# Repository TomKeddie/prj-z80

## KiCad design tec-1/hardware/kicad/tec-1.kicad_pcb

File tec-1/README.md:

# Ideas

## Notes
- Need xtal for clock (issue 14) 8MHZ for Z80A
- display and tape (issue 15 page 47)
- single stepper (issue 15 page 51)
- Z80B can do 6MHz
- Add clock generation to cpld (2/4/6MHz)
- Mux keyboard and ft2232 through cpld for keyboard emulation
- flash A18 is wired to z80 A12 to split the chip in two
- shift button (issue 13 page 10)
- 8x8 display (issue 11 pag 22)
- lcd interface (issue 15 page 49)
- use 74ABT574 for octal latch

## CPLDs
### Address (100%)
- memory address decode and bank select flash
- memory address decode sram x 2
- cpu clock divide
- io address decode for keyboard, led display
- single step

### Data (100%)
- keyboard mux
- led display column store
- speaker

### Peripheral (100%)
- Data bus {8 pins}
- Address bus {3 pins}
- Control bus {2 pins}
- 8x8 led store (x and y) {16 pins}
- io address decode for 8x8 led {no pins}
- io address decode for lcd display {1 pin}
- jmon keyboard {1 pin}

## Memory Map
| Address Range | Purpose | Notes | 
|:-------------:|:-------------:|:-------------|
| 0000-07FF     | 2k ROM | Bank select from 27C040 |
| 0800-17FF     | 4k RAM | Use 1/2 2264 (8k) |
| 1800-1FFF     | 2k ROM | Bank select from 27C040 |
| 2000-2FFF     | 4k RAM | Use 1/2 2264 (8k) |

## IO Map

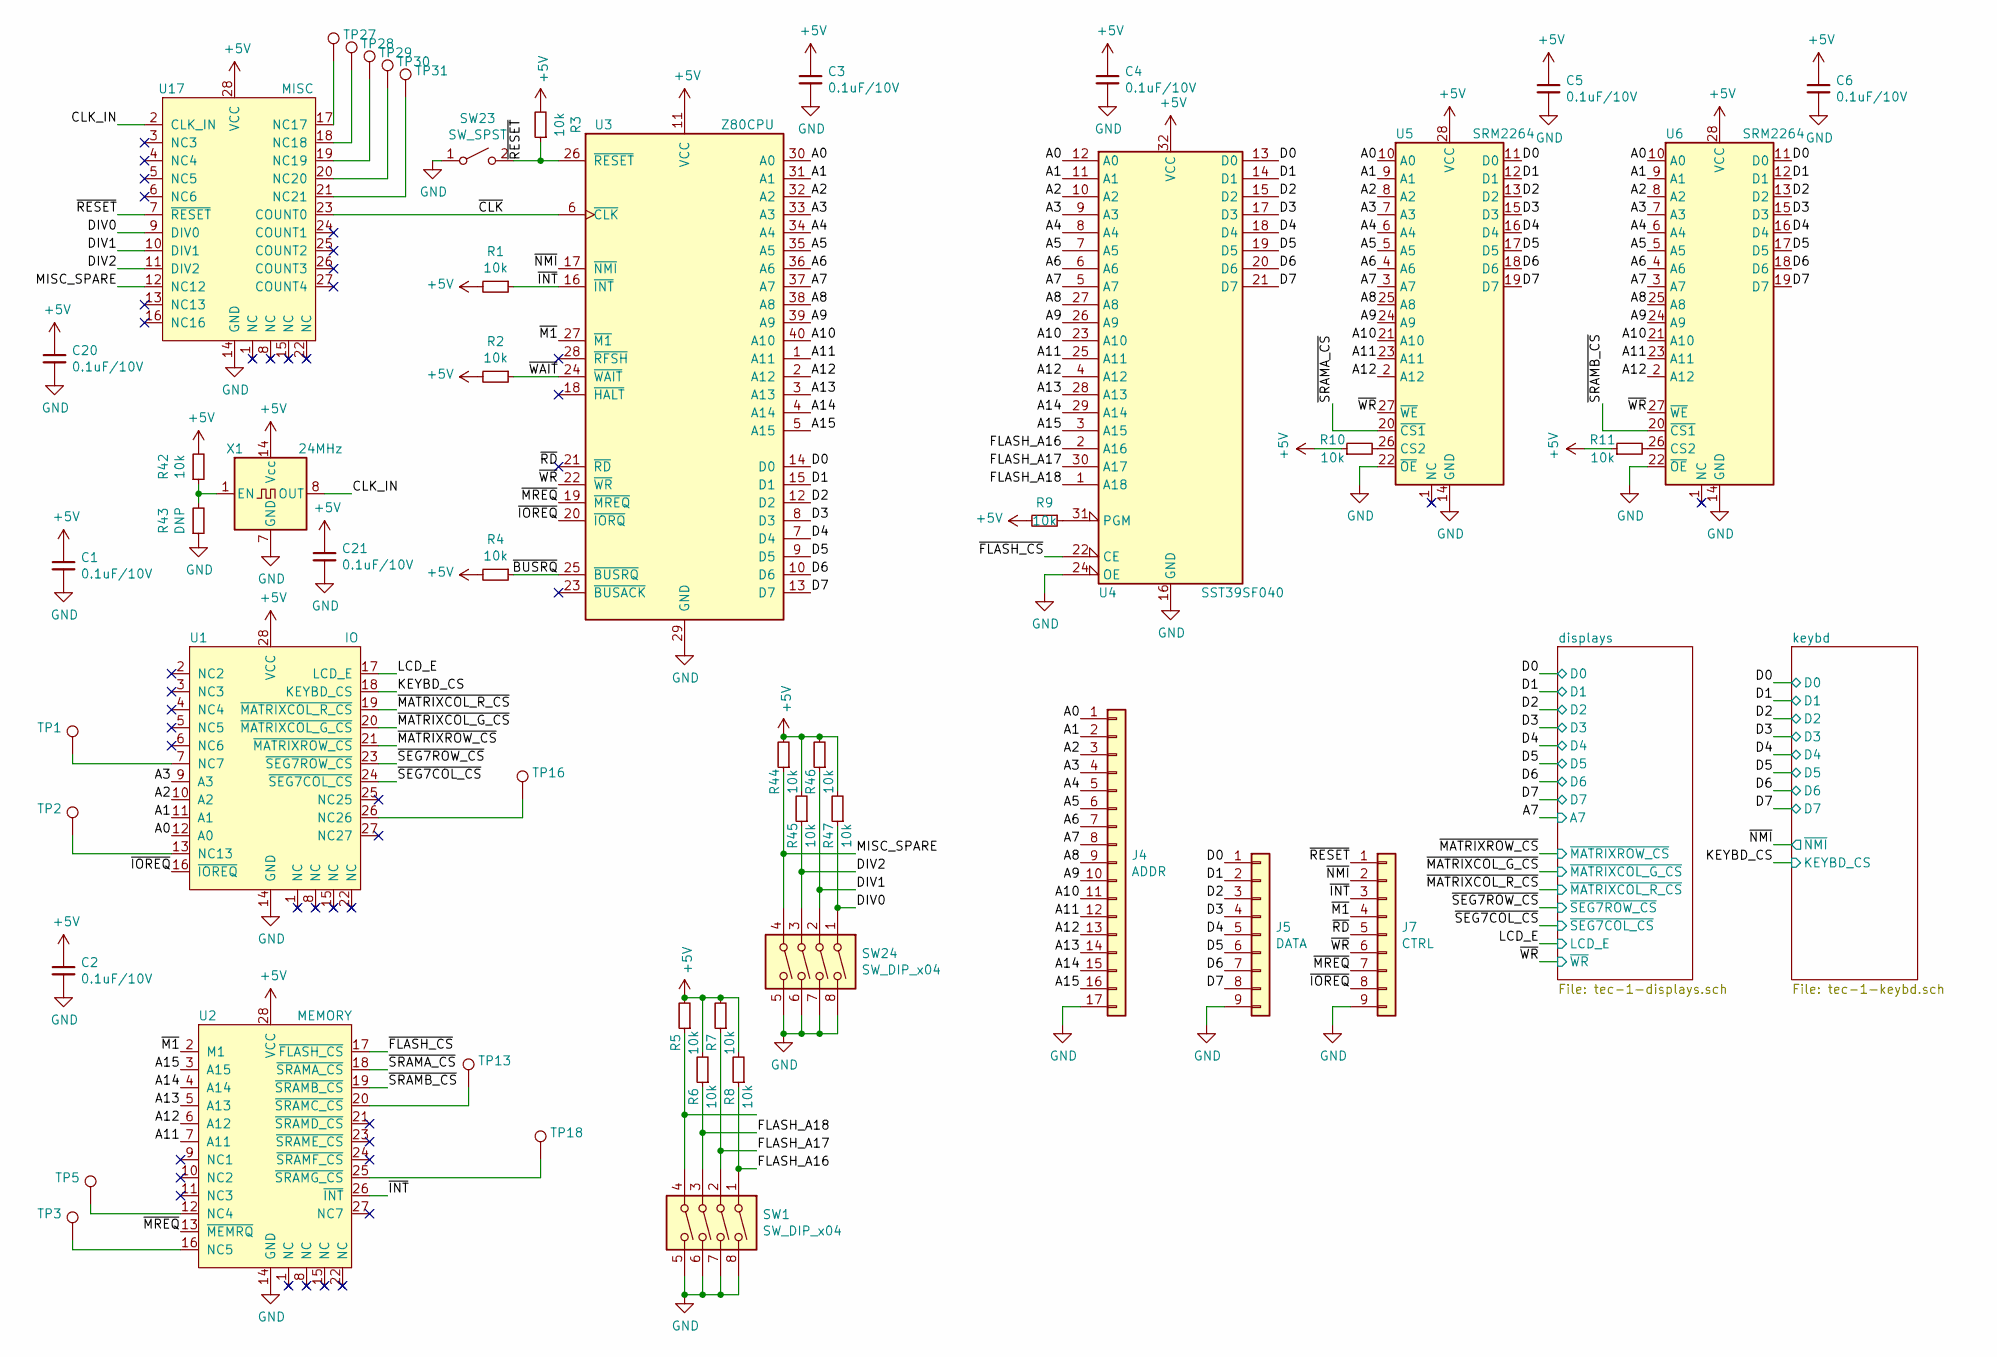
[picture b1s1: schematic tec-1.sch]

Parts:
C1, C2, C3, C4, C5, C6, C20, C21: 0.1uF/10V; C_0805_2012Metric
J4: ADDR; PinHeader_1x17_P2.54mm_Vertical
J5: DATA; PinHeader_1x09_P2.54mm_Vertical
J7: CTRL; PinHeader_1x09_P2.54mm_Vertical
R1, R2, R3, R4, R5, R6, R7, R8, R9, R10, R11, R42, R44, R45, R46, R47: 10k; R_0805_2012Metric
R43: DNP; R_0805_2012Metric
SW1, SW24: SW_DIP_x04; DIP-8_W7.62mm_LongPads
SW23: SW_SPST; SW_12x12_SMD
TP1, TP2, TP3, TP5, TP13, TP16, TP18, TP27, TP28, TP29, TP30, TP31: TestPoint; TestPoint_Pad_D2.0mm
U1: IO; PLCC-28_SMD-Socket
U2: MEMORY; PLCC-28_SMD-Socket
U3: Z80CPU; DIP-40_W15.24mm_LongPads
U4: SST39SF040; PLCC-32_SMD-Socket_9x7
U5, U6: SRM2264; DIP-28_W15.24mm_LongPads
U17: MISC; PLCC-28_SMD-Socket
X1: 24MHz; Oscillator_DIP-14_LargePads

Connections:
+5V: C1.1, C2.1, C3.1, C4.1, C5.1, C6.1, C20.1, C21.1, R1.2, R2.2, R3.2, R4.2, R5.2, R6.2, R7.2, R8.2, R9.2, R10.1, R11.1, R42.2, R44.2, R45.2, R46.2, R47.2, U1.28 (VCC), U2.28 (VCC), U3.11 (VCC), U4.32 (VCC), U5.28 (VCC), U6.28 (VCC), U17.28 (VCC), X1.14 (Vcc); also elsewhere on the board
/A0: J4.1, U1.12 (A0), U3.30 (A0), U4.12 (A0), U5.10 (A0), U6.10 (A0)
/A1: J4.2, U1.11 (A1), U3.31 (A1), U4.11 (A1), U5.9 (A1), U6.9 (A1)
/A2: J4.3, U1.10 (A2), U3.32 (A2), U4.10 (A2), U5.8 (A2), U6.8 (A2)
/A3: J4.4, U1.9 (A3), U3.33 (A3), U4.9 (A3), U5.7 (A3), U6.7 (A3)
/A4: J4.5, U3.34 (A4), U4.8 (A4), U5.6 (A4), U6.6 (A4)
/A5: J4.6, U3.35 (A5), U4.7 (A5), U5.5 (A5), U6.5 (A5)
/A6: J4.7, U3.36 (A6), U4.6 (A6), U5.4 (A6), U6.4 (A6)
/A7: J4.8, U3.37 (A7), U4.5 (A7), U5.3 (A7), U6.3 (A7); also elsewhere on the board
/A8: J4.9, U3.38 (A8), U4.27 (A8), U5.25 (A8), U6.25 (A8)
/A9: J4.10, U3.39 (A9), U4.26 (A9), U5.24 (A9), U6.24 (A9)
/A10: J4.11, U3.40 (A10), U4.23 (A10), U5.21 (A10), U6.21 (A10)
/A11: J4.12, U2.7 (A11), U3.1 (A11), U4.25 (A11), U5.23 (A11), U6.23 (A11)
/A12: J4.13, U2.6 (A12), U3.2 (A12), U4.4 (A12), U5.2 (A12), U6.2 (A12)
/A13: J4.14, U2.5 (A13), U3.3 (A13), U4.28 (A13)
/A14: J4.15, U2.4 (A14), U3.4 (A14), U4.29 (A14)
/A15: J4.16, U2.3 (A15), U3.5 (A15), U4.3 (A15)
/CLK_IN: U17.2 (CLK_IN), X1.8 (OUT)
/D0: J5.1, U3.14 (D0), U4.13 (D0), U5.11 (D0), U6.11 (D0); also elsewhere on the board
/D1: J5.2, U3.15 (D1), U4.14 (D1), U5.12 (D1), U6.12 (D1); also elsewhere on the board
/D2: J5.3, U3.12 (D2), U4.15 (D2), U5.13 (D2), U6.13 (D2); also elsewhere on the board
/D3: J5.4, U3.8 (D3), U4.17 (D3), U5.15 (D3), U6.15 (D3); also elsewhere on the board
/D4: J5.5, U3.7 (D4), U4.18 (D4), U5.16 (D4), U6.16 (D4); also elsewhere on the board
/D5: J5.6, U3.9 (D5), U4.19 (D5), U5.17 (D5), U6.17 (D5); also elsewhere on the board
/D6: J5.7, U3.10 (D6), U4.20 (D6), U5.18 (D6), U6.18 (D6); also elsewhere on the board
/D7: J5.8, U3.13 (D7), U4.21 (D7), U5.19 (D7), U6.19 (D7); also elsewhere on the board
/DIV0: R47.1, SW24.1, U17.9 (DIV0)
/DIV1: R46.1, SW24.2, U17.10 (DIV1)
/DIV2: R45.1, SW24.3, U17.11 (DIV2)
/FLASH_A16: R8.1, SW1.1, U4.2 (A16)
/FLASH_A17: R7.1, SW1.2, U4.30 (A17)
/FLASH_A18: R6.1, SW1.3, U4.1 (A18)
/KEYBD_CS: U1.18 (KEYBD_CS); also elsewhere on the board
/LCD_E: U1.17 (LCD_E); also elsewhere on the board
/MISC_SPARE: R44.1, SW24.4, U17.12 (NC12)
/~BUSRQ: R4.1, U3.25 (~BUSRQ~)
/~CLK: U3.6 (~CLK~), U17.23 (COUNT0)
/~FLASH_CS: U2.17 (~FLASH_CS), U4.22 (CE)
/~INT: J7.3, R1.1, U2.26 (~INT), U3.16 (~INT~)
/~IOREQ: J7.8, U1.16 (~IOREQ), U3.20 (~IORQ~)
/~M1: J7.4, U2.2 (M1), U3.27 (~M1~)
/~MATRIXCOL_G_CS: U1.20 (~MATRIXCOL_G_CS); also elsewhere on the board
/~MATRIXCOL_R_CS: U1.19 (~MATRIXCOL_R_CS); also elsewhere on the board
/~MATRIXROW_CS: U1.21 (~MATRIXROW_CS); also elsewhere on the board
/~MREQ: J7.7, U2.13 (~MEMRQ), U3.19 (~MREQ~)
/~NMI: J7.2, U3.17 (~NMI~); also elsewhere on the board
/~RD: J7.5, U3.21 (~RD~)
/~RESET: J7.1, R3.1, SW23.2 (B), U3.26 (~RESET~), U17.7 (~RESET)
/~SEG7COL_CS: U1.24 (~SEG7COL_CS); also elsewhere on the board
/~SEG7ROW_CS: U1.23 (~SEG7ROW_CS); also elsewhere on the board
/~SRAMA_CS: U2.18 (~SRAMA_CS), U5.20 (~CS1)
/~SRAMB_CS: U2.19 (~SRAMB_CS), U6.20 (~CS1)
/~WAIT: R2.1, U3.24 (~WAIT~)
/~WR: J7.6, U3.22 (~WR~), U5.27 (~WE), U6.27 (~WE); also elsewhere on the board
GND: C1.2, C2.2, C3.2, C4.2, C5.2, C6.2, C20.2, C21.2, J4.17, J5.9, J7.9, R43.1, SW1.5, SW1.6, SW1.7, SW1.8, SW23.1 (A), SW24.5, SW24.6, SW24.7, SW24.8, U1.14 (GND), U2.14 (GND), U3.29 (GND), U4.16 (GND), U4.24 (OE), U5.14 (GND), U5.22 (~OE), U6.14 (GND), U6.22 (~OE), U17.14 (GND), X1.7 (GND); also elsewhere on the board
unnamed: R5.1, SW1.4
unnamed: R9.1, U4.31 (PGM)
unnamed: R10.2, U5.26 (CS2)
unnamed: R11.2, U6.26 (CS2)
unnamed: R42.1, R43.2, X1.1 (EN)
unnamed: TP1.1, U1.7 (NC7)
unnamed: TP2.1, U1.13 (NC13)
unnamed: TP3.1, U2.16 (NC5)
unnamed: TP5.1, U2.12 (NC4)
unnamed: TP13.1, U2.20 (~SRAMC_CS)
unnamed: TP16.1, U1.26 (NC26)
unnamed: TP18.1, U2.25 (~SRAMG_CS)
unnamed: TP27.1, U17.17 (NC17)
unnamed: TP28.1, U17.18 (NC18)
unnamed: TP29.1, U17.19 (NC19)
unnamed: TP30.1, U17.20 (NC20)
unnamed: TP31.1, U17.21 (NC21)

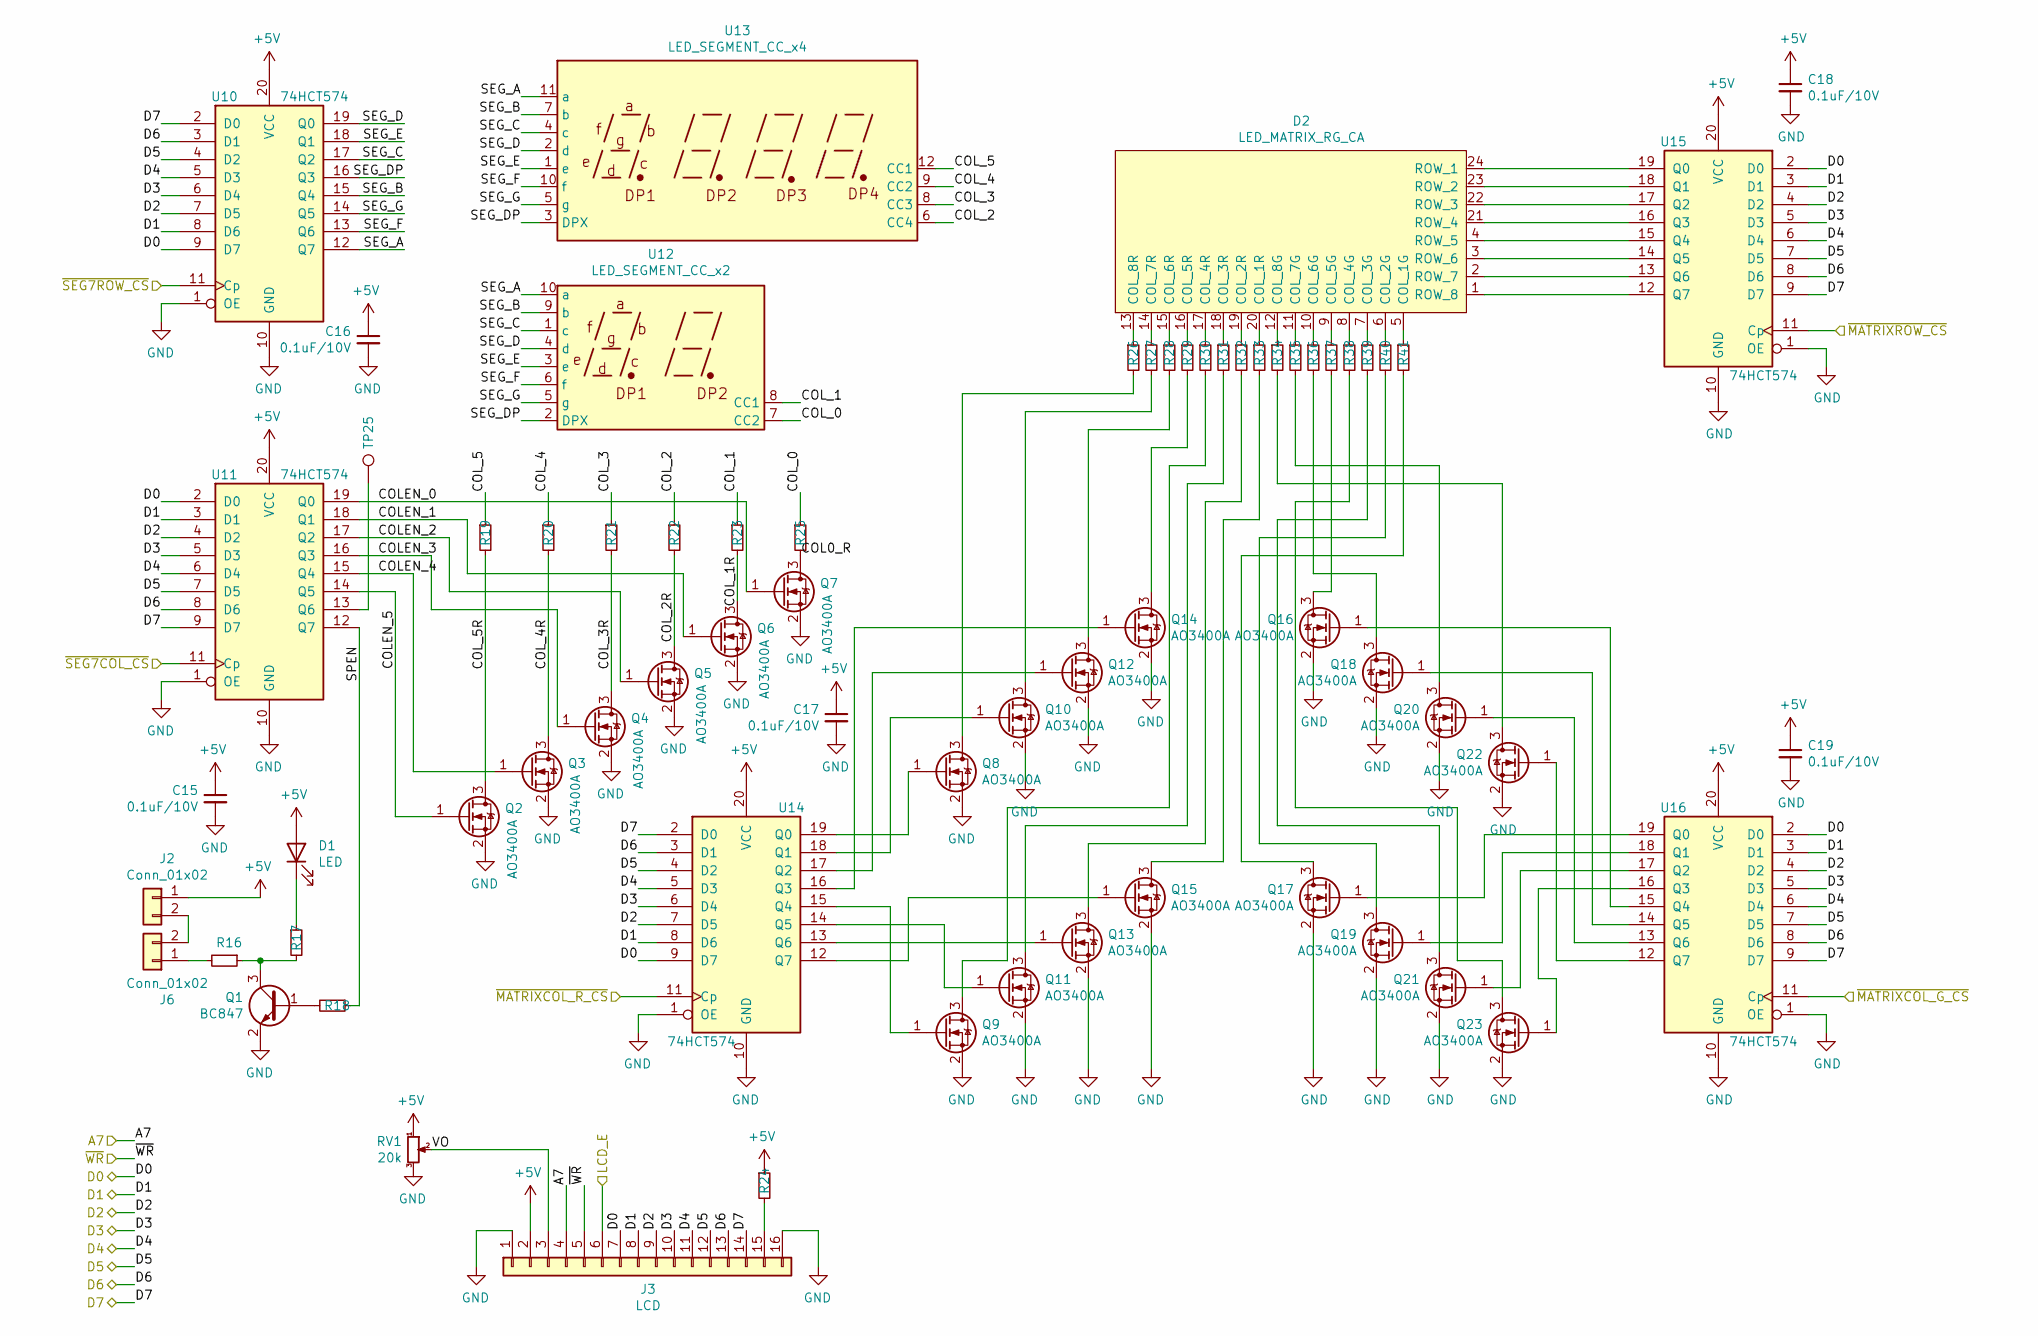
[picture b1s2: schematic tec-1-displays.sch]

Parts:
C15, C16, C17, C18, C19: 0.1uF/10V; C_0805_2012Metric
D1: LED; LED_0805_2012Metric
D2: LED_MATRIX_RG_CA; GYXM-1588AURG
J2: Conn_01x02; JST_PH_S2B-PH-SM4-TB_1x02-1MP_P2.00mm_Horizontal
J3: LCD; PinHeader_1x16_P2.54mm_Horizontal
J6: Conn_01x02; PinHeader_1x02_P2.54mm_Vertical
Q1: BC847; SOT-23
Q2, Q3, Q4, Q5, Q6, Q7, Q8, Q9, Q10, Q11, Q12, Q13, Q14, Q15, Q16, Q17, Q18, Q19, Q20, Q21, Q22, Q23: AO3400A; SOT-23
R16, R19, R20, R21, R22, R23, R24, R25, R26, R27, R28, R29, R30, R31, R32, R33, R34, R35, R36, R37, R38, R39, R40, R41: 100R; R_0805_2012Metric
R17, R18: 1k; R_0805_2012Metric
RV1: 20k; Potentiometer_Bourns_TC33X_Vertical
TP25: TestPoint; TestPoint_Pad_D2.0mm
U10, U11, U14, U15, U16: 74HCT574; SOIC-20W_7.5x12.8mm_P1.27mm
U12: LED_SEGMENT_CC_x2; D5621A-LEDx2
U13: LED_SEGMENT_CC_x4; D5641A-LEDx4

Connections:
+5V: C15.1, C16.1, C17.1, C18.1, C19.1, D1.2 (A), J2.1, J3.2, R24.1, RV1.1, U10.20 (VCC), U11.20 (VCC), U14.20 (VCC), U15.20 (VCC), U16.20 (VCC); also elsewhere on the board
/A7: J3.4; also elsewhere on the board
/D0: J3.7, U10.9 (D7), U11.2 (D0), U14.9 (D7), U15.2 (D0), U16.2 (D0); also elsewhere on the board
/D1: J3.8, U10.8 (D6), U11.3 (D1), U14.8 (D6), U15.3 (D1), U16.3 (D1); also elsewhere on the board
/D2: J3.9, U10.7 (D5), U11.4 (D2), U14.7 (D5), U15.4 (D2), U16.4 (D2); also elsewhere on the board
/D3: J3.10, U10.6 (D4), U11.5 (D3), U14.6 (D4), U15.5 (D3), U16.5 (D3); also elsewhere on the board
/D4: J3.11, U10.5 (D3), U11.6 (D4), U14.5 (D3), U15.6 (D4), U16.6 (D4); also elsewhere on the board
/D5: J3.12, U10.4 (D2), U11.7 (D5), U14.4 (D2), U15.7 (D5), U16.7 (D5); also elsewhere on the board
/D6: J3.13, U10.3 (D1), U11.8 (D6), U14.3 (D1), U15.8 (D6), U16.8 (D6); also elsewhere on the board
/D7: J3.14, U10.2 (D0), U11.9 (D7), U14.2 (D0), U15.9 (D7), U16.9 (D7); also elsewhere on the board
/LCD_E: J3.6; also elsewhere on the board
/displays/COL0_R: Q7.3 (D), R25.2
/displays/COLEN_0: Q7.1 (G), U11.19 (Q0)
/displays/COLEN_1: Q6.1 (G), U11.18 (Q1)
/displays/COLEN_2: Q5.1 (G), U11.17 (Q2)
/displays/COLEN_3: Q4.1 (G), U11.16 (Q3)
/displays/COLEN_4: Q3.1 (G), U11.15 (Q4)
/displays/COLEN_5: Q2.1 (G), U11.14 (Q5)
/displays/COL_0: R25.1, U12.7 (CC2)
/displays/COL_1: R23.1, U12.8 (CC1)
/displays/COL_1R: Q6.3 (D), R23.2
/displays/COL_2: R22.1, U13.6 (CC4)
/displays/COL_2R: Q5.3 (D), R22.2
/displays/COL_3: R21.1, U13.8 (CC3)
/displays/COL_3R: Q4.3 (D), R21.2
/displays/COL_4: R20.1, U13.9 (CC2)
/displays/COL_4R: Q3.3 (D), R20.2
/displays/COL_5: R19.1, U13.12 (CC1)
/displays/COL_5R: Q2.3 (D), R19.2
/displays/SEG_A: U10.12 (Q7), U12.10 (a), U13.11 (a)
/displays/SEG_B: U10.15 (Q4), U12.9 (b), U13.7 (b)
/displays/SEG_C: U10.17 (Q2), U12.1 (c), U13.4 (c)
/displays/SEG_D: U10.19 (Q0), U12.4 (d), U13.2 (d)
/displays/SEG_DP: U10.16 (Q3), U12.2 (DPX), U13.3 (DPX)
/displays/SEG_E: U10.18 (Q1), U12.3 (e), U13.1 (e)
/displays/SEG_F: U10.13 (Q6), U12.6 (f), U13.10 (f)
/displays/SEG_G: U10.14 (Q5), U12.5 (g), U13.5 (g)
/displays/SPEN: R18.1, U11.12 (Q7)
/displays/VO: J3.3, RV1.2
/~MATRIXCOL_G_CS: U16.11 (Cp); also elsewhere on the board
/~MATRIXCOL_R_CS: U14.11 (Cp); also elsewhere on the board
/~MATRIXROW_CS: U15.11 (Cp); also elsewhere on the board
/~SEG7COL_CS: U11.11 (Cp); also elsewhere on the board
/~SEG7ROW_CS: U10.11 (Cp); also elsewhere on the board
/~WR: J3.5; also elsewhere on the board
GND: C15.2, C16.2, C17.2, C18.2, C19.2, J3.1, J3.16, Q1.2 (E), Q2.2 (S), Q3.2 (S), Q4.2 (S), Q5.2 (S), Q6.2 (S), Q7.2 (S), Q8.2 (S), Q9.2 (S), Q10.2 (S), Q11.2 (S), Q12.2 (S), Q13.2 (S), Q14.2 (S), Q15.2 (S), Q16.2 (S), Q17.2 (S), Q18.2 (S), Q19.2 (S), Q20.2 (S), Q21.2 (S), Q22.2 (S), Q23.2 (S), RV1.3, U10.1 (OE), U10.10 (GND), U11.1 (OE), U11.10 (GND), U14.1 (OE), U14.10 (GND), U15.1 (OE), U15.10 (GND), U16.1 (OE), U16.10 (GND); also elsewhere on the board
unnamed: D1.1 (K), R17.1
unnamed: D2.1 (ROW_8), U15.12 (Q7)
unnamed: D2.2 (ROW_7), U15.13 (Q6)
unnamed: D2.3 (ROW_6), U15.14 (Q5)
unnamed: D2.4 (ROW_5), U15.15 (Q4)
unnamed: D2.5 (COL_1G), R41.1
unnamed: D2.6 (COL_2G), R40.1
unnamed: D2.7 (COL_3G), R39.1
unnamed: D2.8 (COL_4G), R38.1
unnamed: D2.9 (COL_5G), R37.1
unnamed: D2.10 (COL_6G), R36.1
unnamed: D2.11 (COL_7G), R35.1
unnamed: D2.12 (COL_8G), R34.1
unnamed: D2.13 (COL_8R), R26.1
unnamed: D2.14 (COL_7R), R27.1
unnamed: D2.15 (COL_6R), R28.1
unnamed: D2.16 (COL_5R), R29.1
unnamed: D2.17 (COL_4R), R30.1
unnamed: D2.18 (COL_3R), R31.1
unnamed: D2.19 (COL_2R), R32.1
unnamed: D2.20 (COL_1R), R33.1
unnamed: D2.21 (ROW_4), U15.16 (Q3)
unnamed: D2.22 (ROW_3), U15.17 (Q2)
unnamed: D2.23 (ROW_2), U15.18 (Q1)
unnamed: D2.24 (ROW_1), U15.19 (Q0)
unnamed: J2.2, J6.2
unnamed: J3.15, R24.2
unnamed: J6.1, R16.2
unnamed: Q1.1 (B), R18.2
unnamed: Q1.3 (C), R16.1, R17.2
unnamed: Q8.1 (G), U14.19 (Q0)
unnamed: Q8.3 (D), R26.2
unnamed: Q9.1 (G), U14.15 (Q4)
unnamed: Q9.3 (D), R30.2
unnamed: Q10.1 (G), U14.18 (Q1)
unnamed: Q10.3 (D), R27.2
unnamed: Q11.1 (G), U14.14 (Q5)
unnamed: Q11.3 (D), R31.2
unnamed: Q12.1 (G), U14.17 (Q2)
unnamed: Q12.3 (D), R28.2
unnamed: Q13.1 (G), U14.13 (Q6)
unnamed: Q13.3 (D), R32.2
unnamed: Q14.1 (G), U14.16 (Q3)
unnamed: Q14.3 (D), R29.2
unnamed: Q15.1 (G), U14.12 (Q7)
unnamed: Q15.3 (D), R33.2
unnamed: Q16.1 (G), U16.15 (Q4)
unnamed: Q16.3 (D), R37.2
unnamed: Q17.1 (G), U16.19 (Q0)
unnamed: Q17.3 (D), R41.2
unnamed: Q18.1 (G), U16.14 (Q5)
unnamed: Q18.3 (D), R36.2
unnamed: Q19.1 (G), U16.18 (Q1)
unnamed: Q19.3 (D), R40.2
unnamed: Q20.1 (G), U16.13 (Q6)
unnamed: Q20.3 (D), R35.2
unnamed: Q21.1 (G), U16.17 (Q2)
unnamed: Q21.3 (D), R39.2
unnamed: Q22.1 (G), U16.12 (Q7)
unnamed: Q22.3 (D), R34.2
unnamed: Q23.1 (G), U16.16 (Q3)
unnamed: Q23.3 (D), R38.2
unnamed: TP25.1, U11.13 (Q6)

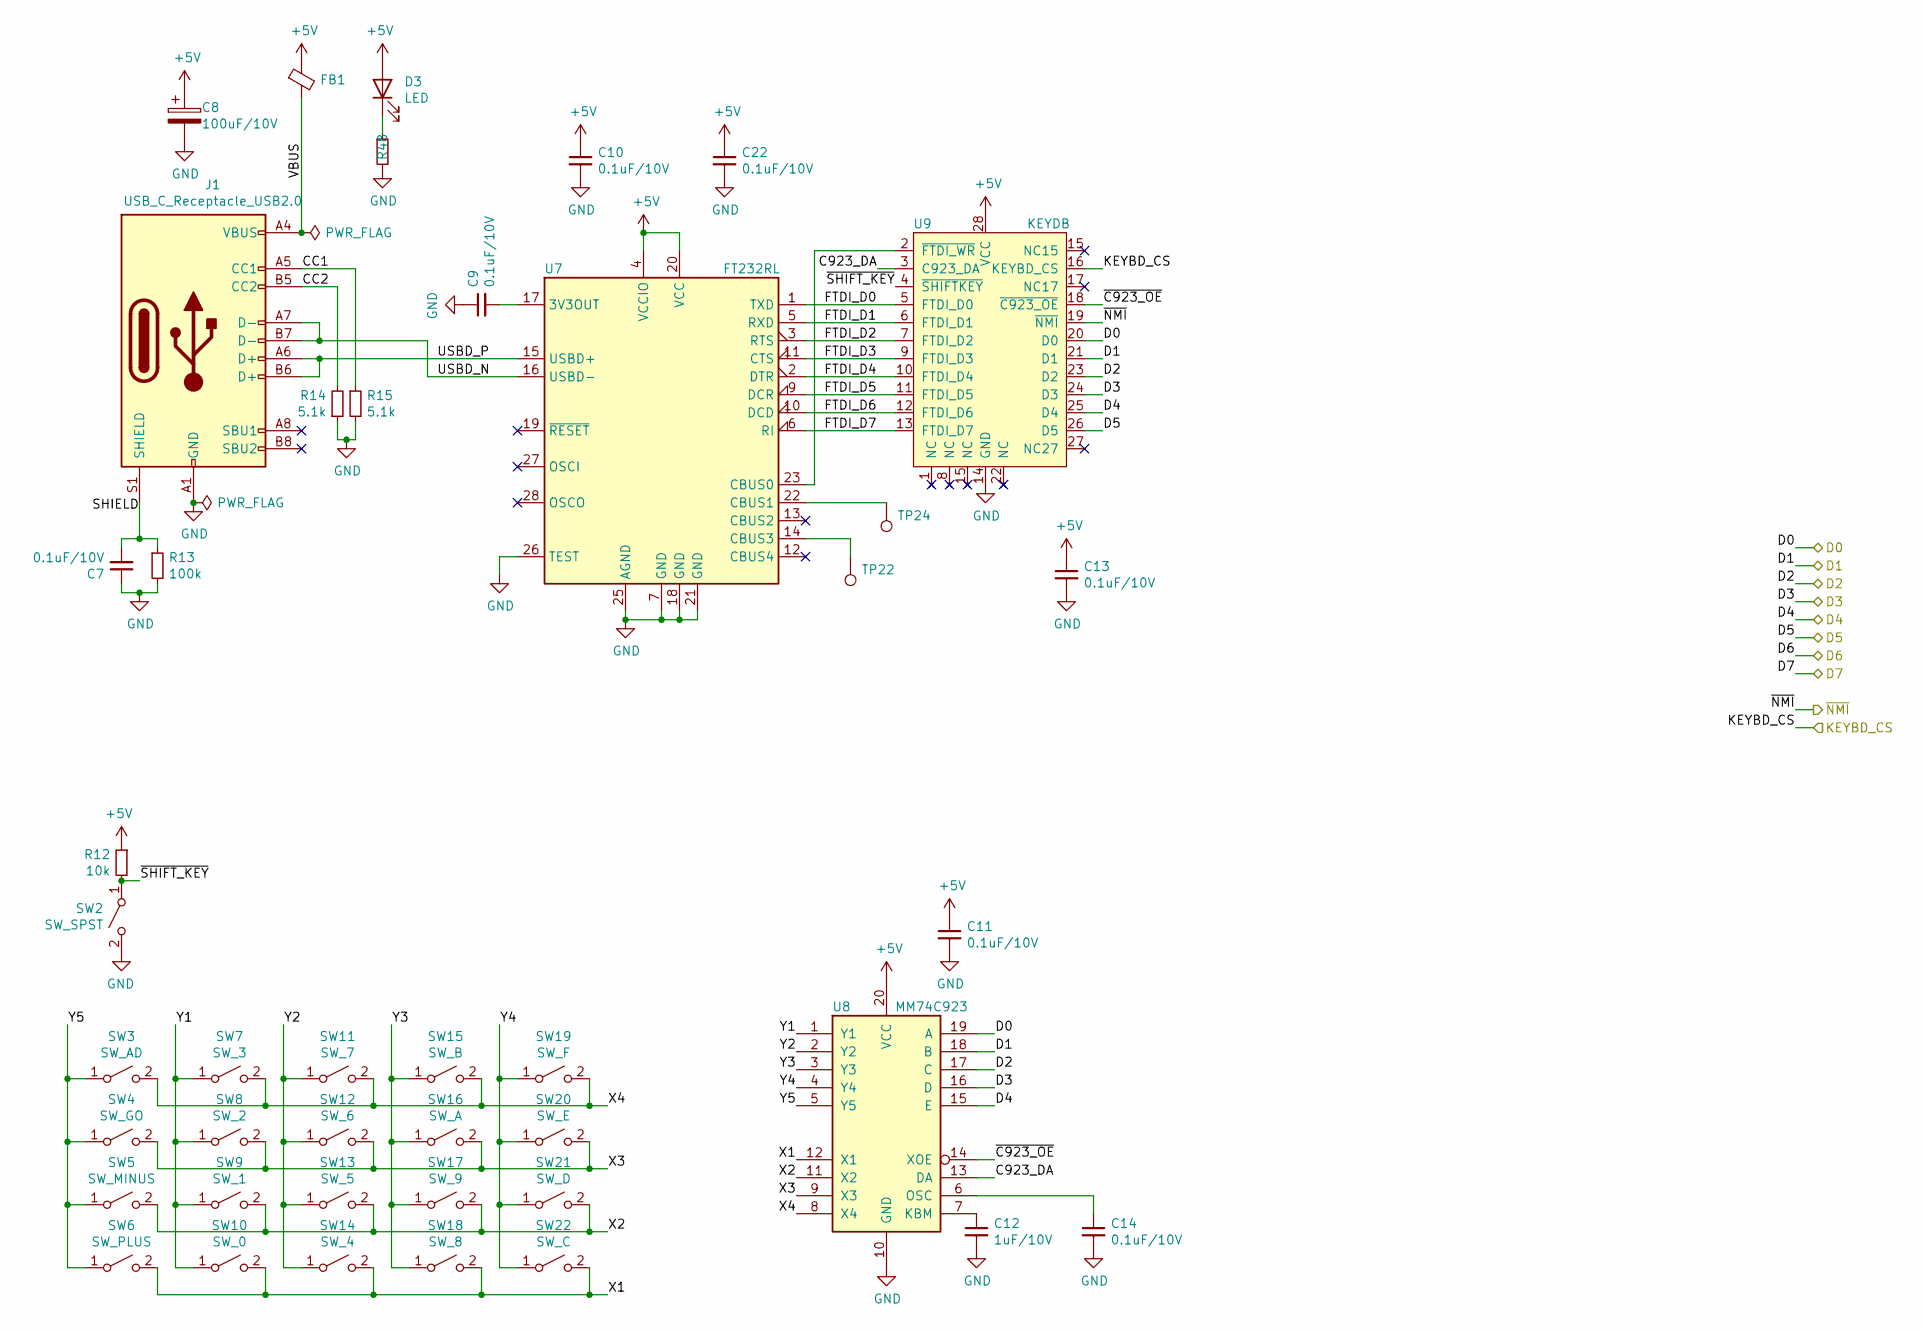
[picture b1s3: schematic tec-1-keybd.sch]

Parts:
C7, C9, C10, C11, C13, C14, C22: 0.1uF/10V; C_0805_2012Metric
C8: 100uF/10V; CP_EIA-7343-31_Kemet-D
C12: 1uF/10V; C_0805_2012Metric
D3: LED; LED_0805_2012Metric
FB1: Ferrite_Bead_Small; L_0805_2012Metric
J1: USB_C_Receptacle_USB2.0; USB_C_Receptacle_GT-USB-7010
R12: 10k; R_0805_2012Metric
R13: 100k; R_0805_2012Metric
R14, R15: 5.1k; R_0805_2012Metric
R48: 1k; R_0805_2012Metric
SW2: SW_SPST; SW_12x12_SMD
SW3: SW_AD; SW_12x12_SMD
SW4: SW_GO; SW_12x12_SMD
SW5: SW_MINUS; SW_12x12_SMD
SW6: SW_PLUS; SW_12x12_SMD
SW7: SW_3; SW_12x12_SMD
SW8: SW_2; SW_12x12_SMD
SW9: SW_1; SW_12x12_SMD
SW10: SW_0; SW_12x12_SMD
SW11: SW_7; SW_12x12_SMD
SW12: SW_6; SW_12x12_SMD
SW13: SW_5; SW_12x12_SMD
SW14: SW_4; SW_12x12_SMD
SW15: SW_B; SW_12x12_SMD
SW16: SW_A; SW_12x12_SMD
SW17: SW_9; SW_12x12_SMD
SW18: SW_8; SW_12x12_SMD
SW19: SW_F; SW_12x12_SMD
SW20: SW_E; SW_12x12_SMD
SW21: SW_D; SW_12x12_SMD
SW22: SW_C; SW_12x12_SMD
TP22, TP24: TestPoint; TestPoint_Pad_D2.0mm
U7: FT232RL; SSOP-28_5.3x10.2mm_P0.65mm
U8: MM74C923; DIP-20_W7.62mm_LongPads
U9: KEYDB; PLCC-28_SMD-Socket

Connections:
+5V: C8.1, C10.1, C11.1, C13.1, C22.1, D3.2 (A), FB1.1, R12.1, U7.4 (VCCIO), U7.20 (VCC), U8.20 (VCC), U9.28 (VCC); also elsewhere on the board
/D0: U8.19 (A), U9.20 (D0); also elsewhere on the board
/D1: U8.18 (B), U9.21 (D1); also elsewhere on the board
/D2: U8.17 (C), U9.23 (D2); also elsewhere on the board
/D3: U8.16 (D), U9.24 (D3); also elsewhere on the board
/D4: U8.15 (E), U9.25 (D4); also elsewhere on the board
/D5: U9.26 (D5); also elsewhere on the board
/KEYBD_CS: U9.16 (KEYBD_CS); also elsewhere on the board
/keybd/C923_DA: U8.13 (DA), U9.3 (C923_DA)
/keybd/CC1: J1.A5 (CC1), R15.1
/keybd/CC2: J1.B5 (CC2), R14.2
/keybd/FTDI_D0: U7.1 (TXD), U9.5 (FTDI_D0)
/keybd/FTDI_D1: U7.5 (RXD), U9.6 (FTDI_D1)
/keybd/FTDI_D2: U7.3 (RTS), U9.7 (FTDI_D2)
/keybd/FTDI_D3: U7.11 (CTS), U9.9 (FTDI_D3)
/keybd/FTDI_D4: U7.2 (DTR), U9.10 (FTDI_D4)
/keybd/FTDI_D5: U7.9 (DCR), U9.11 (FTDI_D5)
/keybd/FTDI_D6: U7.10 (DCD), U9.12 (FTDI_D6)
/keybd/FTDI_D7: U7.6 (RI), U9.13 (FTDI_D7)
/keybd/SHIELD: C7.2, J1.S1 (SHIELD), R13.1
/keybd/USBD_N: J1.A7 (D-), J1.B7 (D-), U7.16 (USBD-)
/keybd/USBD_P: J1.A6 (D+), J1.B6 (D+), U7.15 (USBD+)
/keybd/VBUS: FB1.2, J1.A4 (VBUS), J1.A9 (VBUS), J1.B4 (VBUS), J1.B9 (VBUS)
/keybd/X1: SW6.2 (B), SW10.2 (B), SW14.2 (B), SW18.2 (B), SW22.2 (B), U8.12 (X1)
/keybd/X2: SW5.2 (B), SW9.2 (B), SW13.2 (B), SW17.2 (B), SW21.2 (B), U8.11 (X2)
/keybd/X3: SW4.2 (B), SW8.2 (B), SW12.2 (B), SW16.2 (B), SW20.2 (B), U8.9 (X3)
/keybd/X4: SW3.2 (B), SW7.2 (B), SW11.2 (B), SW15.2 (B), SW19.2 (B), U8.8 (X4)
/keybd/Y1: SW7.1 (A), SW8.1 (A), SW9.1 (A), SW10.1 (A), U8.1 (Y1)
/keybd/Y2: SW11.1 (A), SW12.1 (A), SW13.1 (A), SW14.1 (A), U8.2 (Y2)
/keybd/Y3: SW15.1 (A), SW16.1 (A), SW17.1 (A), SW18.1 (A), U8.3 (Y3)
/keybd/Y4: SW19.1 (A), SW20.1 (A), SW21.1 (A), SW22.1 (A), U8.4 (Y4)
/keybd/Y5: SW3.1 (A), SW4.1 (A), SW5.1 (A), SW6.1 (A), U8.5 (Y5)
/keybd/~C923_OE: U8.14 (XOE), U9.18 (~C923_OE)
/keybd/~SHIFT_KEY: R12.2, SW2.1 (A), U9.4 (~SHIFTKEY)
/~NMI: U9.19 (~NMI); also elsewhere on the board
GND: C7.1, C8.2, C9.1, C10.2, C11.2, C12.2, C13.2, C14.2, C22.2, J1.A1 (GND), J1.A12 (GND), J1.B1 (GND), J1.B12 (GND), R13.2, R14.1, R15.2, R48.2, SW2.2 (B), U7.7 (GND), U7.18 (GND), U7.21 (GND), U7.25 (AGND), U7.26 (TEST), U8.10 (GND), U9.14 (GND); also elsewhere on the board
unnamed: C9.2, U7.17 (3V3OUT)
unnamed: C12.1, U8.7 (KBM)
unnamed: C14.1, U8.6 (OSC)
unnamed: D3.1 (K), R48.1
unnamed: TP22.1, U7.14 (CBUS3)
unnamed: TP24.1, U7.22 (CBUS1)
unnamed: U7.23 (CBUS0), U9.2 (~FTDI_WR)

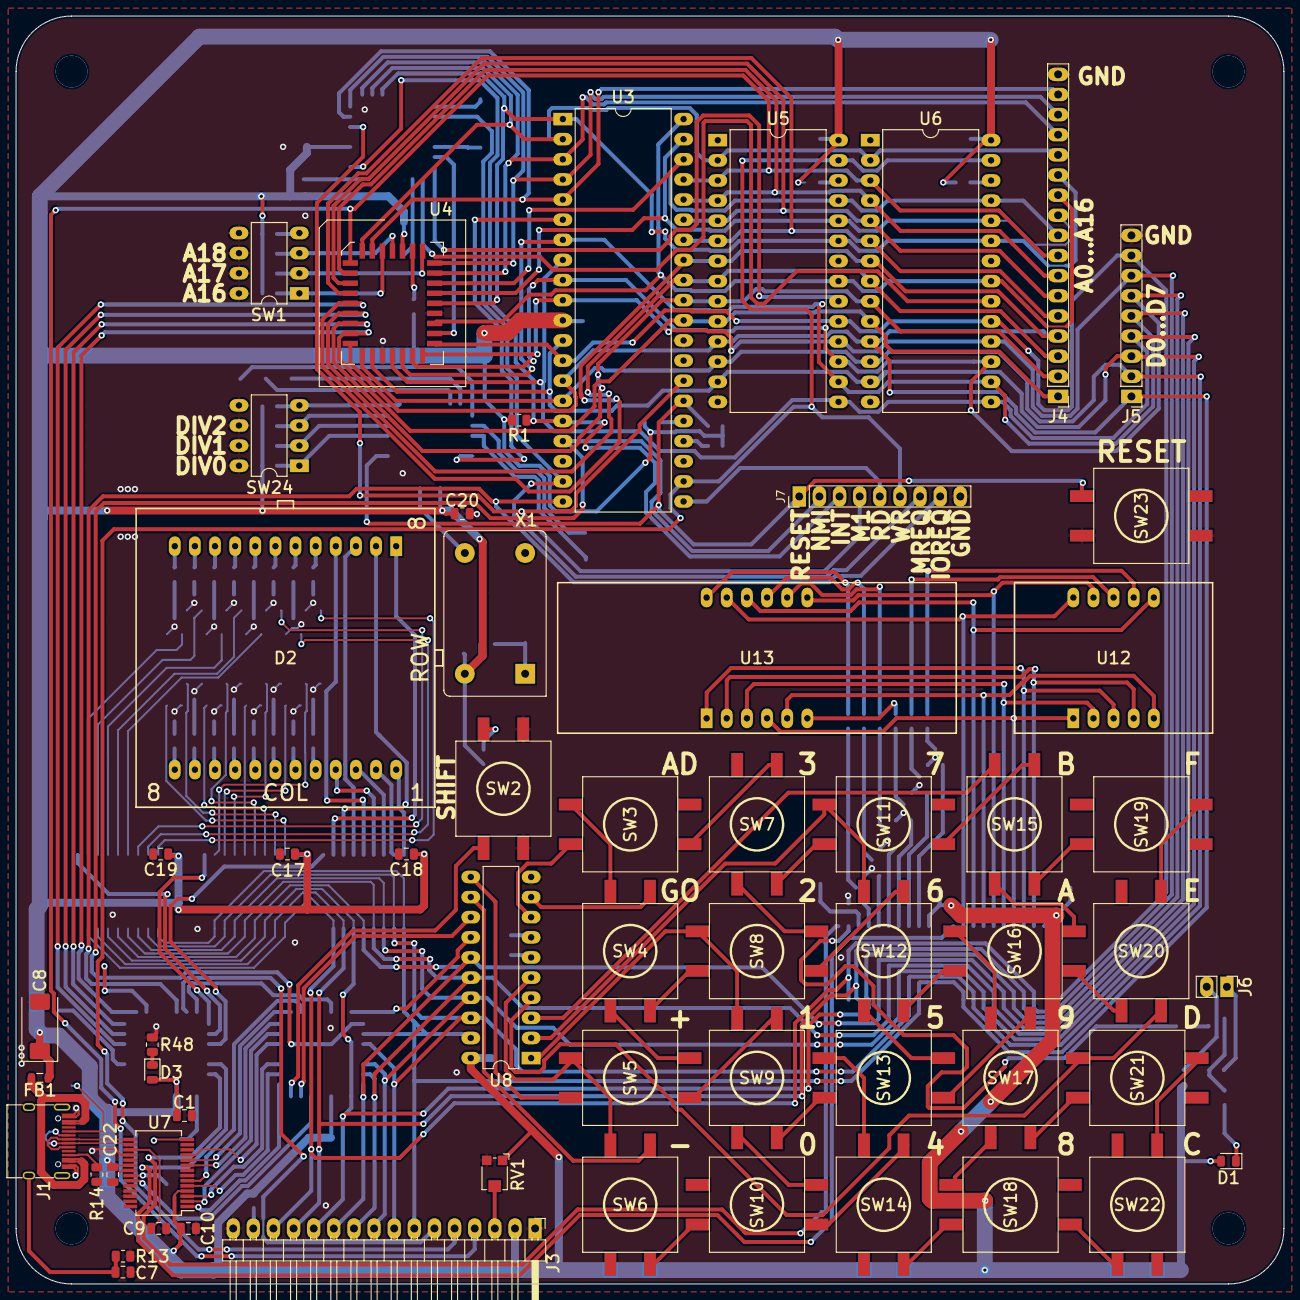
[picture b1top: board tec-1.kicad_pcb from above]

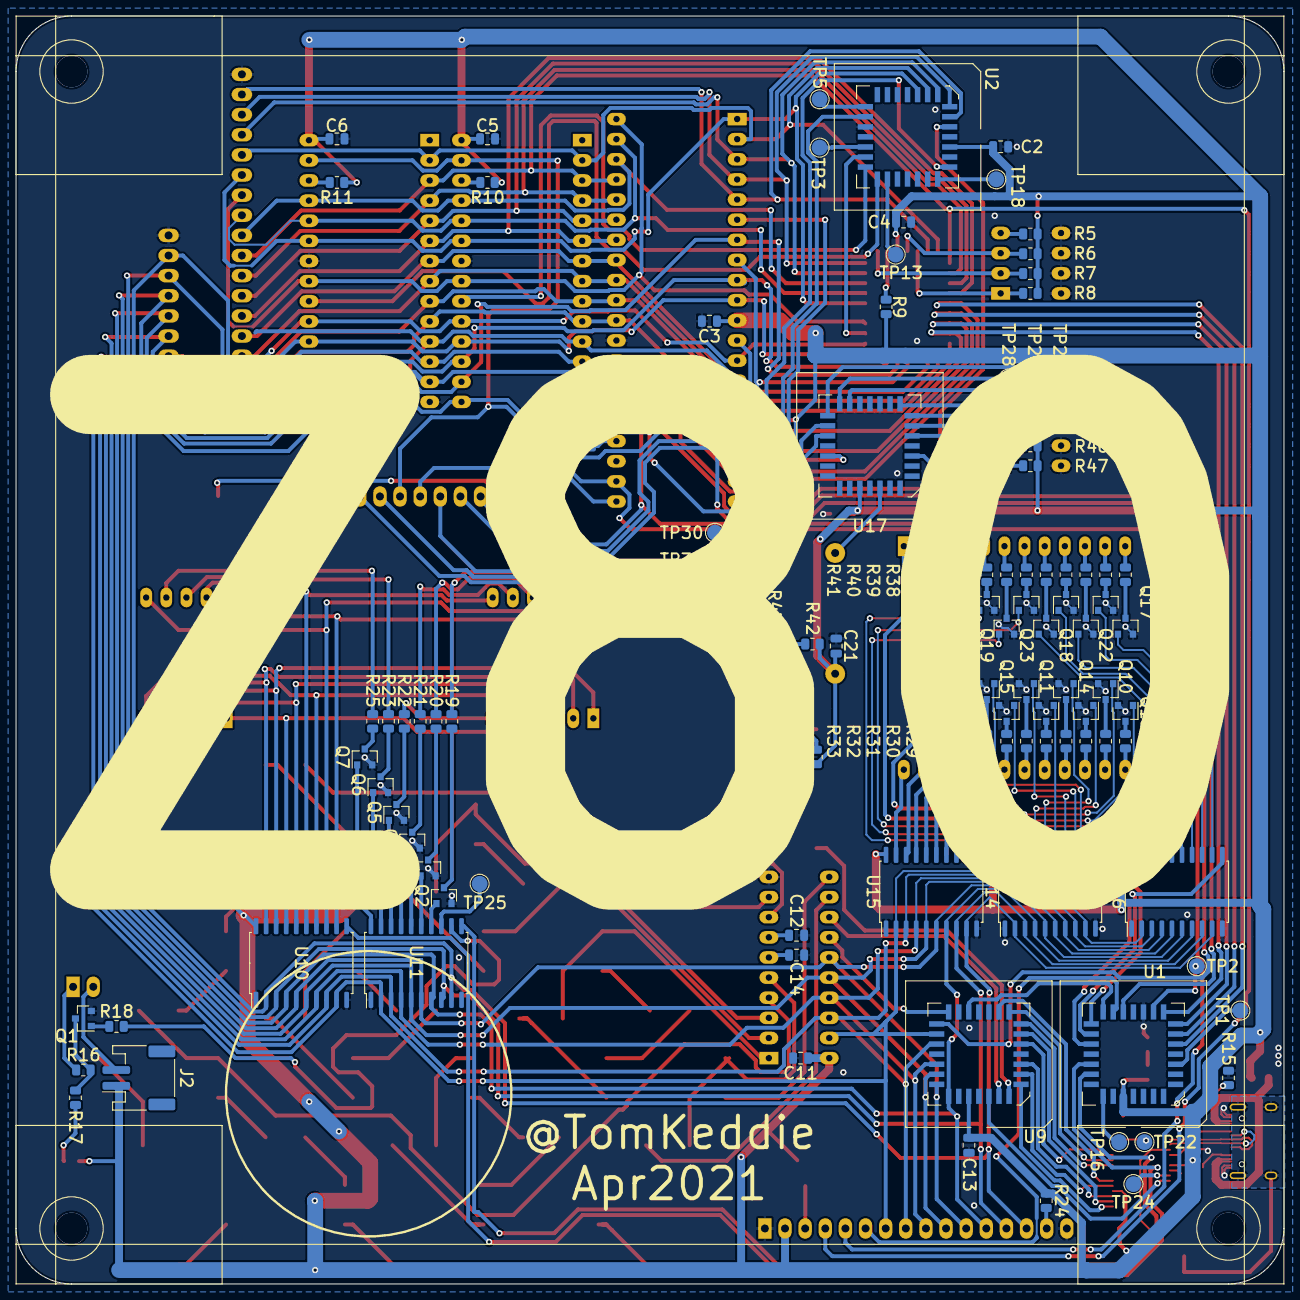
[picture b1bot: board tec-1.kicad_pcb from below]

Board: 2 copper layers, 160.0 x 160.0 mm, 162 parts (104 on the bottom side), 196 nets.

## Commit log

2021-03-22 tec-1: add TE issues 10-12
2021-03-22 tec-1: add TE issues 13-15
2021-03-22 tec-1: added ROMs
2021-03-23 hardware/cpld_a: add address decoder cpld
2021-03-24 hardware/cpld_a: progress commit
2021-03-24 tec-1/hardware/cpld_d: progress commit (too many pins)
2021-03-24 tec-1/hardware/cpld_p: progress commit (no speaker)
2021-03-28 tec-1: address and keyb gal source
2021-03-28 tec-1/hardware: progress checkin for schematic
2021-03-29 hardware/gals: update header on address pld
2021-03-29 tec-1/hardware: add address pld outputs
2021-03-30 tec-1/hardware: add IO pld
2021-03-30 tec-1/hardware: add spares to io gal
2021-03-30 tec-1/hardware: rename address gal to memory gal
2021-03-30 tec-1/hardware: add srec_cat commands to combine roms into flash image
2021-04-02 tec-1/hardware/gals: split projects into subdirectories
2021-04-04 tec-1/hardware/kicad: progress checkin
2021-04-05 tec-1/hardware/gals: fix keybd compilation crash
2021-04-10 tec-1/hardware/gals/misc: progress commit, single bit counter works
2021-04-11 hardware/gals/misc: progress commit, 3 bit divider (sims with X)
2021-04-11 hardware/gals/misc: progress commit, 4 bit divider (doesn't fit)
2021-04-11 tec-1/hardware/gals/misc: clock divider complete
2021-04-11 tec-1/hardware/kicad: progress checkin - add clock & 207 unrouted
2021-04-14 tec-1/hardware/gals: complete and verified against pcb
2021-04-14 tec-1/datasheets: new data sheets
2021-04-14 tec-1/hardware/kicad: routing complete, all DRC errors checked as ok
2021-04-15 tec-1/hardware/kicad: added ctrl header, fixed keypad alignment
2021-04-15 tec-1/hardware/kicad: apr2021 release
2021-04-26 tec-1/hardware/kicad: regenerate Apr2021 release with missing edge cuts included
2021-08-05 hardware/gals: change IO to use palasm4, added simulation, all working
2021-08-07 hardware/gals: change MEMORY to use palasm4, added simulation, all address decodes working
2021-08-11 tec-1/hardware/gals: add single step logic to memory gal, all done
2021-08-11 tec-1/hardware/gals: add palasm4 version of keybd gal, sim working
2021-09-05 hardware/gals: add MISC1.PDS/SIM, misc pld as state machine
2021-09-05 hardware/gals: add working MISC1 design and aborted MISC design
2021-09-05 Add galasm compiler (not used)
2021-09-07 hardware/gals: fix misc1 gal, div pinning was wrong, add /32
2021-09-10 hardware/flash: add binary flash file
2021-09-18 tec-1/python: add first steps of tec-1 python utility
2021-10-13 hardware/gals: first working ftdi driven keyboard
2021-10-15 hardware/gals/keybd: cleanup nmi generation
2021-10-15 tec-1/hardware/gals/keybd: first pass at working keypad, need to flip D6
2021-10-23 keybd: works driven by ftdi but misses some keystrokes
2021-10-25 TEC-1-ROMs/Mon-1B: add mon1B-tom
2021-11-01 tec-1/python: cleanup tec-1.py add active low shift key support
2021-11-03 tec-1/hardware/gals/memory: add SW1_1 support to switch flash with ram
2021-11-03 tec-1/hardware/gals/memory: invert SW1_1 polarity
2021-11-14 tec-1/examples: add issue11_page29_1
